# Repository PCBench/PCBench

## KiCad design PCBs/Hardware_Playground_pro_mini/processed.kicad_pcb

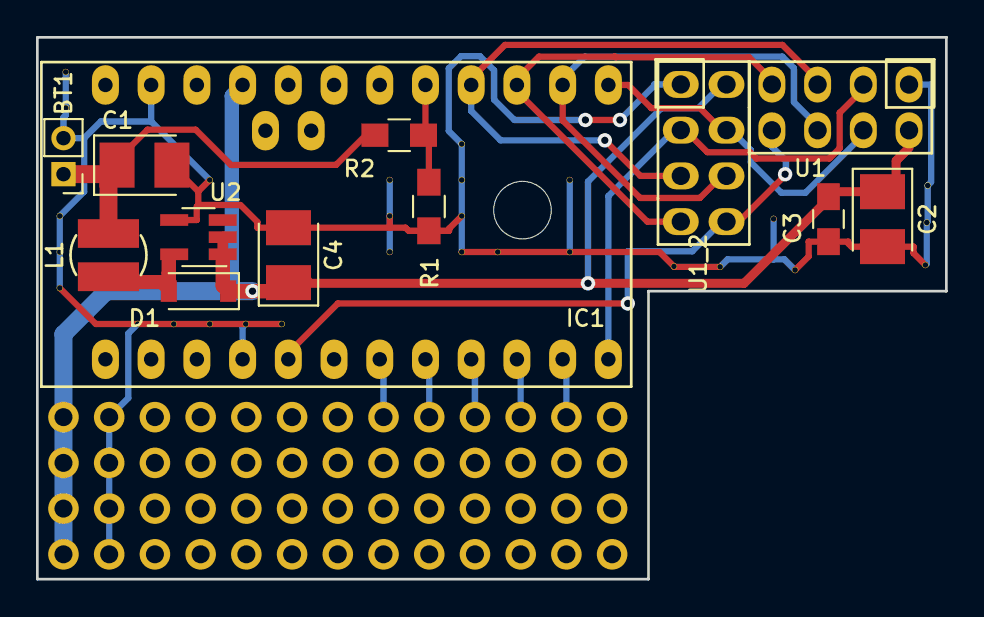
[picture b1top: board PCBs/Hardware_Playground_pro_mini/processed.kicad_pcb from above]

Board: 2 copper layers, 50.5 x 30.1 mm, 41 parts (0 on the bottom side), 11 nets.

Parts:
BT1: 3V; Pin_Header_Straight_1x02_Pitch2.00mm
C1: 10u; CP_Tantalum_Case-B_EIA-3528-21_Reflow
C2: 22u; CP_Tantalum_Case-B_EIA-3528-21_Reflow
C3: 100n; C_0805_HandSoldering
C4: 68u; CP_Tantalum_Case-B_EIA-3528-21_Reflow
D1: 1N5819; D_SOD-123
IC1: ArduinoProMini; pro_mini
L1: 47u; SDR0302
R1: 10K; R_0805_HandSoldering
R2: 22K; R_0805_HandSoldering
U1, U1_2: NRF24L01
U2: NCP1402; SOT-23-5_HandSoldering
V7_1, V7_2, V7_5, V7_6, V7_7, V9_8, V10_8, V11_4, V11_8, V12_8, V13_8, V16_4, V16_5, V16_6, V18_3, V18_4, V18_5, V18_6, V18_6_2, V18_6_3, V18_6_4, V18_6_5, V18_6_6, V18_6_7, V18_6_8, V19_6, V21_4, V21_6: AUTO_VIA; VIA_MATRIX

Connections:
+3.3V: C2.1, C3.1, C4.1, D1.1, IC1.21, U1.2, U1_2.2, U2.1, U2.2
/RF_CE: IC1.12, U1.3, U1_2.3
/RF_CSN: IC1.13, U1.4, U1_2.4
/RF_IRQ: IC1.5, U1.8, U1_2.8
/RF_MISO: IC1.15, U1.7, U1_2.7
/RF_MOSI: IC1.14, U1.6, U1_2.6
/RF_SCK: IC1.16, U1.5, U1_2.5
/V_BATT: IC1.17, R1.2, R2.2
GND: BT1.2, C1.2, C2.2, C3.2, C4.2, IC1.4, IC1.23, R1.1, U1.1, U1_2.1, U2.4, V7_1.1, V7_2.1, V7_5.1, V7_6.1, V7_7.1, V9_8.1, V10_8.1, V11_4.1, V11_8.1, V12_8.1, V13_8.1, V16_4.1, V16_5.1, V16_6.1, V18_3.1, V18_4.1, V18_5.1, V18_6.1, V18_6_2.1, V18_6_3.1, V18_6_4.1, V18_6_5.1, V18_6_6.1, V18_6_7.1, V18_6_8.1, V19_6.1, V21_4.1, V21_6.1
unnamed: BT1.1, C1.1, L1.1, R2.1
unnamed: D1.2, L1.2, U2.5

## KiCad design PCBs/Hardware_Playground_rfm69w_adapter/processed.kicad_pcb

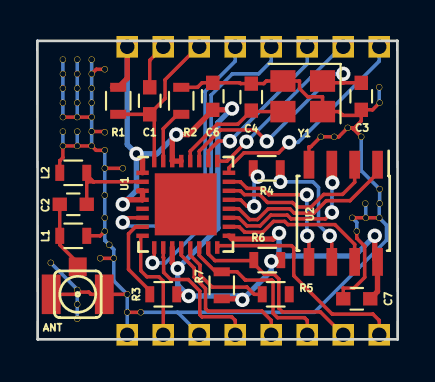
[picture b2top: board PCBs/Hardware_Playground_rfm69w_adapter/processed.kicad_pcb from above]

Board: 2 copper layers, 20.0 x 16.6 mm, 87 parts (0 on the bottom side), 29 nets.

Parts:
ANT: Antenna_Shield; coaxial_u.fl-r-smt-1
C1: 1u; C_0603
C2: 5p6; C_0603
C3, C4: 10p; C_0603
C6: 10u; C_0603
C7: 100n; C_0603
J1, J2, J3, J4, J5, J6, J7, J8, J9, J10, J11, J12, J13, J14, J15, J16: Conn_01x01; Pin_Header_Straight_1x01_Pitch2.00mm
L1, L2: DNP; L_0603
R1, R3, R5, R6, R7: 10K; R_0603
R2: 12K; R_0603
R4: 200; R_0603
U1: ESP8266EX; QFN-32-1EP_5x5mm_Pitch0.5mm
U2: AT25SF321-SSHDB; SOIC-8_3.9x4.9mm_Pitch1.27mm
V2_4, V2_5, V2_6, V2_7, V2_8, V2_9, V2_10, V3_4, V3_5, V3_6, V3_7, V3_8, V3_9, V3_10, V3_20, V3_21, V3_22, V4_4, V4_5, V4_5_2, V4_6, V4_7, V4_8, V4_9, V4_9_2, V4_10, V5_11, V5_11_2, V5_11_3, V7_21, V7_21_2, V7_21_3, V7_21_4, V7_21_5, V7_21_6, V7_21_7, V7_21_8, V7_21_9, V7_21_10, V22_9, V22_9_2, V22_9_3, V22_9_4, V22_9_5, V23_14, V23_14_2, V23_14_3, V23_14_4, V23_14_5, V24_7, V24_13, V24_14: AUTO_VIA; VIA_MATRIX
Y1: 26MHz; Crystal_SMD_3225-4pin_3.2x2.5mm

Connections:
+3V3: C6.2, C7.2, J9.1, R1.1, R3.1, R6.1, R7.1, U1.1, U1.3, U1.4, U1.11, U1.17, U1.29, U1.30, U2.8
/ADC: J15.1, U1.6
/DTR: C1.1, J13.1
/GPIO0: J8.1, R6.2, U1.15
/GPIO2: J1.1, R7.2, U1.14
/GPIO4: J2.1, U1.16
/GPIO5: J3.1, U1.24
/GPIO12: J4.1, U1.10
/GPIO13: J5.1, U1.12
/GPIO14: J6.1, U1.9
/GPIO16: J7.1, U1.8
/LNA: C2.2, L2.1, U1.2
/RESET: C1.2, J10.1, R1.2, U1.32
/SD_CLK: R4.1, U2.6
/SD_CS: U1.20, U2.1
/SD_HD: U1.18, U2.7
/SD_SI: U1.23, U2.5
/SD_SO: U1.22, U2.2
/SD_WP: U1.19, U2.3
/U0RX: J11.1, U1.26
/U0TX: J14.1, U1.25
GND: ANT.2, C3.2, C4.2, C6.1, C7.1, J12.1, J16.1, L1.2, L2.2, R2.1, U2.4, V2_4.1, V2_5.1, V2_6.1, V2_7.1, V2_8.1, V2_9.1, V2_10.1, V3_4.1, V3_5.1, V3_6.1, V3_7.1, V3_8.1, V3_9.1, V3_10.1, V3_20.1, V3_21.1, V3_22.1, V4_4.1, V4_5.1, V4_5_2.1, V4_6.1, V4_7.1, V4_8.1, V4_9.1, V4_9_2.1, V4_10.1, V5_11.1, V5_11_2.1, V5_11_3.1, V7_21.1, V7_21_2.1, V7_21_3.1, V7_21_4.1, V7_21_5.1, V7_21_6.1, V7_21_7.1, V7_21_8.1, V7_21_9.1, V7_21_10.1, V22_9.1, V22_9_2.1, V22_9_3.1, V22_9_4.1, V22_9_5.1, V23_14.1, V23_14_2.1, V23_14_3.1, V23_14_4.1, V23_14_5.1, V24_7.1, V24_13.1, V24_14.1, Y1.2, Y1.4
unnamed: ANT.1, C2.1, L1.1
unnamed: C3.1, U1.27, Y1.1
unnamed: C4.1, U1.28, Y1.3
unnamed: R2.2, U1.31
unnamed: R3.2, U1.7
unnamed: R4.2, U1.21
unnamed: R5.1, U1.13

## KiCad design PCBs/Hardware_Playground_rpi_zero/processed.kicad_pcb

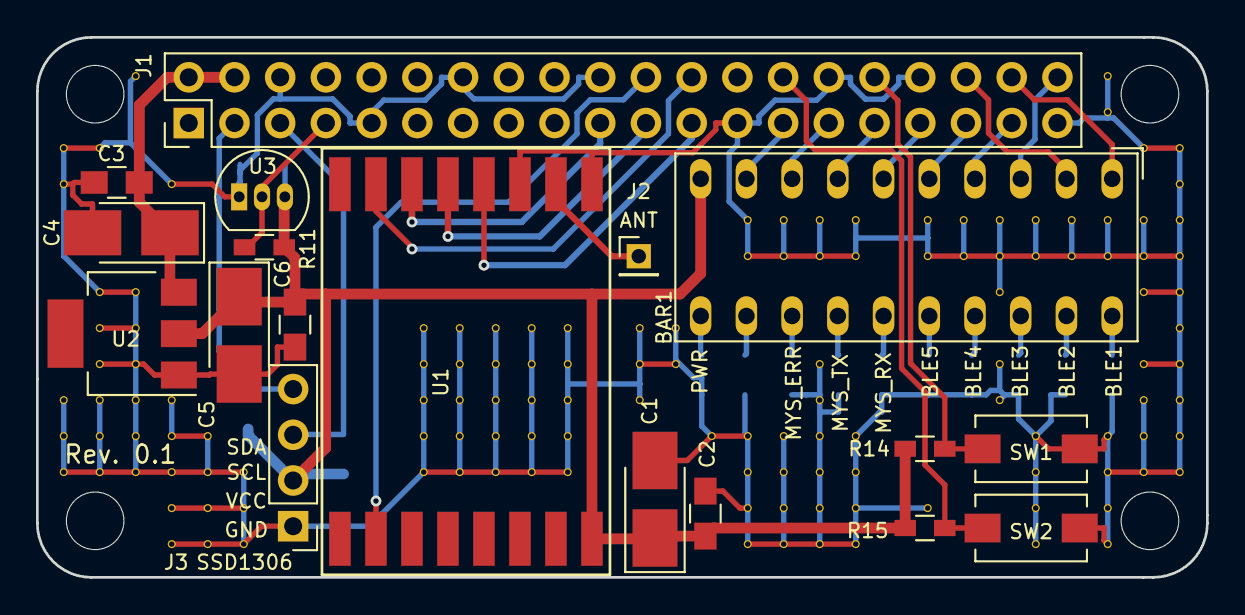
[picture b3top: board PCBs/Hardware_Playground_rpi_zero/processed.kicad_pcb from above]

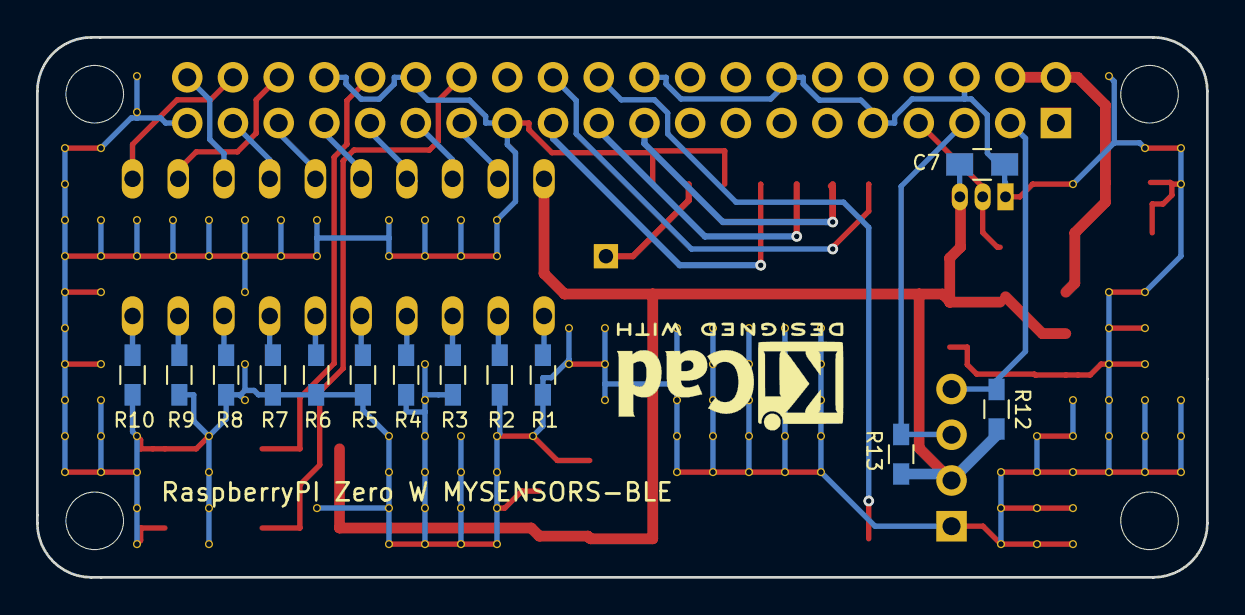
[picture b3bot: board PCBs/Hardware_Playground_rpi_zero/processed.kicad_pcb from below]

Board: 2 copper layers, 65.0 x 30.0 mm, 164 parts (13 on the bottom side), 33 nets.

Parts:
BAR1: HDSP-4850_2; HDSP-4850
C1, C4, C5: 22u; CP_Tantalum_Case-B_EIA-3528-21_Hand
C2, C3, C6, C7: 100n; C_0805_HandSoldering
J1: RPI_Zero_W; Pin_Header_Straight_2x20_Pitch2.54mm
J2: ANT; Pin_Header_Straight_1x01_Pitch2.00mm
J3: SSD1306; Pin_Header_Straight_1x04_Pitch2.54mm
R1, R2, R3, R4, R5, R6, R7, R8, R9, R10: 220; R_0603_HandSoldering
R11, R12, R13: 4K7; R_0603_HandSoldering
R14, R15: 10K; R_0603_HandSoldering
SW1, SW2: BLE; SW_SPST_EVQPE1
U1: RFM69HW; RFM69HW_SMD_Handsoldering
U2: AMS1117; SOT-223
U3: DS18B20; TO-92_Inline_Narrow_Oval
V3_4, V3_5, V3_11, V3_12, V3_13, V4_4, V4_8, V4_9, V4_10, V4_11, V4_12, V4_13, V5_2, V5_8, V5_9, V5_10, V5_11, V5_12, V5_13, V6_5, V6_11, V6_12, V6_13, V6_14, V6_15, V7_12, V7_13, V7_14, V7_15, V8_13, V8_14, V8_15, V13_9, V13_10, V13_11, V13_12, V13_13, V14_9, V14_10, V14_11, V14_12, V14_13, V15_9, V15_10, V15_11, V15_12, V15_13, V16_9, V16_10, V16_11, V16_12, V16_13, V17_9, V17_10, V17_11, V17_12, V17_13, V19_9, V19_10, V19_11, V20_9, V20_10, V21_12, V22_6, V22_7, V22_12, V22_13, V22_14, V22_15, V23_6, V23_7, V23_12, V23_13, V23_14, V23_15, V24_6, V24_7, V24_10, V24_11, V24_12, V24_13, V24_14, V24_15, V25_6, V25_7, V25_12, V25_13, V25_14, V25_15, V27_6, V27_7, V27_14, V28_6, V28_7, V29_6, V29_7, V29_8, V29_10, V29_11, V30_6, V30_7, V30_12, V30_13, V30_14, V30_15, V31_6, V31_7, V32_2, V32_3, V32_6, V32_7, V32_12, V32_13, V32_14, V32_15, V33_4, V33_6, V33_7, V33_8, V33_10, V33_11, V33_12, V33_13, V34_4, V34_5, V34_6, V34_7, V34_8, V34_9, V34_10, V34_11, V34_12, V34_13: AUTO_VIA; VIA_MATRIX

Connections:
+3V3: BAR1.10, C1.1, C2.2, C5.1, C6.2, C7.1, J3.2, R11.1, R12.2, R13.2, R14.1, R15.1, U1.8, U2.2, U3.3
+5V: C3.2, C4.1, J1.2, J1.4, U2.3
/RFM69_CE: J1.22, U1.2
/RFM69_CS: J1.24, U1.15
/RFM69_MISO: J1.21, U1.13
/RFM69_MOSI: J1.19, U1.14
/RFM69_SCK: J1.23, U1.12
/SSD_SCL: J1.5, J3.3, R13.1
/SSD_SDA: J1.3, J3.4, R12.1
/SW1: J1.32, R14.2, SW1.1
/SW2: J1.28, R15.2, SW2.1
GND: C1.2, C2.1, C3.1, C4.2, C5.2, C6.1, C7.2, J1.6, J1.9, J1.14, J1.20, J1.25, J1.30, J1.34, J1.39, J3.1, R1.2, R2.2, R3.2, R4.2, R5.2, R6.2, R7.2, R8.2, R9.2, R10.2, SW1.2, SW2.2, U1.9, U1.11, U2.1, U3.1, V3_4.1, V3_5.1, V3_11.1, V3_12.1, V3_13.1, V4_4.1, V4_8.1, V4_9.1, V4_10.1, V4_11.1, V4_12.1, V4_13.1, V5_2.1, V5_8.1, V5_9.1, V5_10.1, V5_11.1, V5_12.1, V5_13.1, V6_5.1, V6_11.1, V6_12.1, V6_13.1, V6_14.1, V6_15.1, V7_12.1, V7_13.1, V7_14.1, V7_15.1, V8_13.1, V8_14.1, V8_15.1, V13_9.1, V13_10.1, V13_11.1, V13_12.1, V13_13.1, V14_9.1, V14_10.1, V14_11.1, V14_12.1, V14_13.1, V15_9.1, V15_10.1, V15_11.1, V15_12.1, V15_13.1, V16_9.1, V16_10.1, V16_11.1, V16_12.1, V16_13.1, V17_9.1, V17_10.1, V17_11.1, V17_12.1, V17_13.1, V19_9.1, V19_10.1, V19_11.1, V20_9.1, V20_10.1, V21_12.1, V22_6.1, V22_7.1, V22_12.1, V22_13.1, V22_14.1, V22_15.1, V23_6.1, V23_7.1, V23_12.1, V23_13.1, V23_14.1, V23_15.1, V24_6.1, V24_7.1, V24_10.1, V24_11.1, V24_12.1, V24_13.1, V24_14.1, V24_15.1, V25_6.1, V25_7.1, V25_12.1, V25_13.1, V25_14.1, V25_15.1, V27_6.1, V27_7.1, V27_14.1, V28_6.1, V28_7.1, V29_6.1, V29_7.1, V29_8.1, V29_10.1, V29_11.1, V30_6.1, V30_7.1, V30_12.1, V30_13.1, V30_14.1, V30_15.1, V31_6.1, V31_7.1, V32_2.1, V32_3.1, V32_6.1, V32_7.1, V32_12.1, V32_13.1, V32_14.1, V32_15.1, V33_4.1, V33_6.1, V33_7.1, V33_8.1, V33_10.1, V33_11.1, V33_12.1, V33_13.1, V34_4.1, V34_5.1, V34_6.1, V34_7.1, V34_8.1, V34_9.1, V34_10.1, V34_11.1, V34_12.1, V34_13.1
unnamed: BAR1.1, J1.38
unnamed: BAR1.2, J1.36
unnamed: BAR1.3, J1.40
unnamed: BAR1.4, J1.37
unnamed: BAR1.5, J1.35
unnamed: BAR1.6, J1.33
unnamed: BAR1.7, J1.31
unnamed: BAR1.8, J1.29
unnamed: BAR1.9, J1.27
unnamed: BAR1.11, R1.1
unnamed: BAR1.12, R2.1
unnamed: BAR1.13, R3.1
unnamed: BAR1.14, R4.1
unnamed: BAR1.15, R5.1
unnamed: BAR1.16, R6.1
unnamed: BAR1.17, R7.1
unnamed: BAR1.18, R8.1
unnamed: BAR1.19, R9.1
unnamed: BAR1.20, R10.1
unnamed: J1.7, R11.2, U3.2
unnamed: J2.1, U1.10

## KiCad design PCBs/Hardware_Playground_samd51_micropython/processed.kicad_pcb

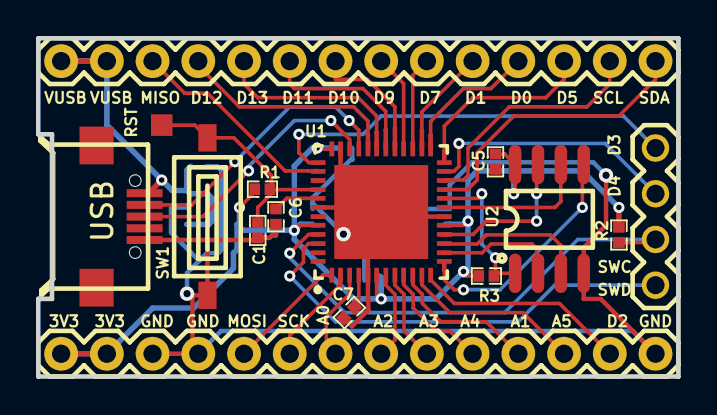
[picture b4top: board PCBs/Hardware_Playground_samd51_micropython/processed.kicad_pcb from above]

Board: 2 copper layers, 35.6 x 18.8 mm, 21 parts (0 on the bottom side), 39 nets.

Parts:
C1, C2, C3, C4, C7, C8, C9, C10: 1uF; 0402
C5: 100nF; 0402
C6: 10uF; 0402
H2: Header-Male-2.54_1x4; 210S-1X4P
JP1, JP2: M14; 1X14
R1: 10K; 0402
R2: 2K2; 0402
R3: 100K; 0402
SW1: RESET; SWITCH-3X6X2.5_SMD
U1: ATSAMD51G19A-MU; 48QFN7X7
U2: IS25LP016D-JBLE; SOIC-8
U3: AP2112K-3.3TRG1; SOT-25
USB: Micro USB-B 5P_C40942; MICRO-USB-12

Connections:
+3V3: C3.2, C4.1, C5.2, C8.1, C9.1, C10.2, JP2.13, JP2.14, R1.2, R2.2, R3.2, U1.6, U1.17, U1.36, U1.44, U2.8, U3.5
A0: JP2.8, U1.3
A1: JP2.4, U1.10
A2: JP2.7, U1.7
A3: JP2.6, U1.8
A4: JP2.5, U1.9
A5: JP2.3, U1.11
AREF: C7.1, U1.4
D2: JP2.2, U1.12
D3: H2.4, U1.37
D4: H2.3, U1.23
D5: JP1.12, U1.24
D7: JP1.9, U1.27
D9: JP1.8, U1.28
D10: JP1.7, U1.29
D11: JP1.6, U1.30
D12: JP1.4, U1.32
D13: JP1.5, U1.31
D+: U1.34, USB.3
D-: U1.33, USB.2
GND: C1.1, C2.2, C3.1, C4.2, C6.1, C7.2, C8.2, C9.2, C10.1, JP2.1, JP2.11, JP2.12, SW1.1, U1.5, U1.18, U1.35, U1.42, U1.49, U2.4, U3.2, USB.5
MISO: JP1.3, U1.38
MOSI: JP2.10, U1.1
QSPI_CS: R3.1, U1.20, U2.1
QSPI_DAT0: U1.13, U2.5
QSPI_DAT1: U1.14, U2.2
QSPI_DAT2: U1.15, U2.3
QSPI_DAT3: U1.16, U2.7
QSPI_SCK: U1.19, U2.6
RST: C1.2, R1.1, SW1.2, U1.40
RX_D0: JP1.11, U1.25
SCK: JP2.9, U1.2
SCL: JP1.13, U1.22
SDA: JP1.14, U1.21
SWCLK: H2.2, R2.1, U1.45
SWDIO: H2.1, U1.46
TX_D1: JP1.10, U1.26
U1_41: C6.2, U1.41
VUSB: C2.1, JP1.1, JP1.2, U3.1, U3.3, USB.1

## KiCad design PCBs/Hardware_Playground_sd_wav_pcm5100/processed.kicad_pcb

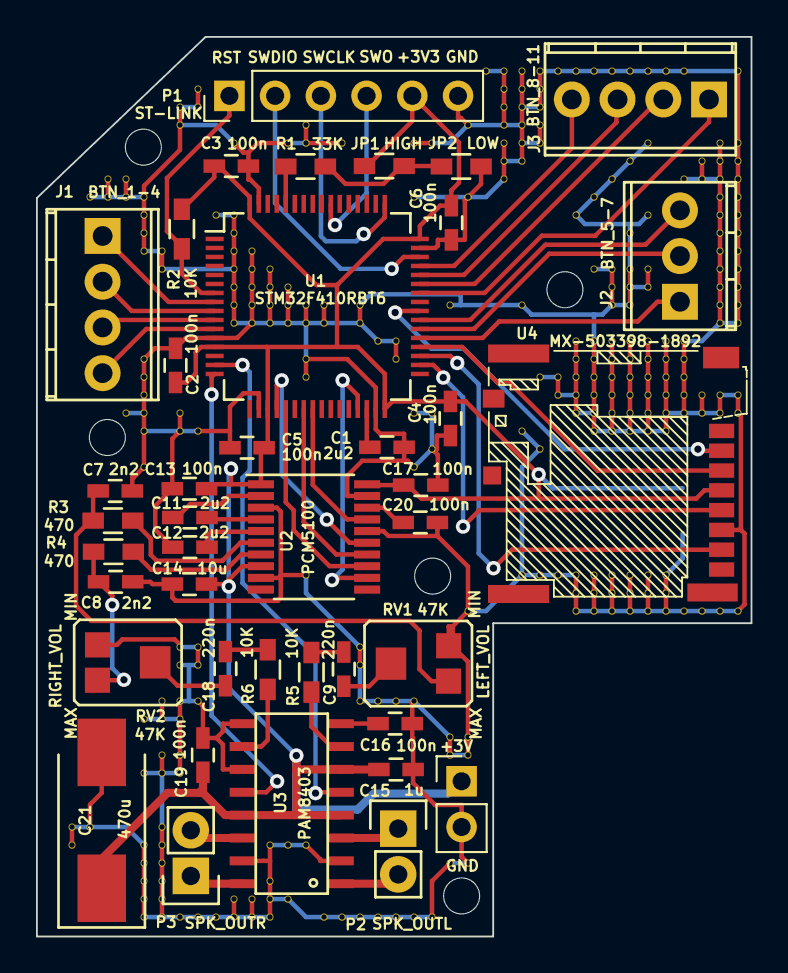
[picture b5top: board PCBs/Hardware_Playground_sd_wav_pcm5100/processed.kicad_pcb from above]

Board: 2 copper layers, 39.7 x 50.0 mm, 323 parts (1 on the bottom side), 50 nets.

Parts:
C1, C11, C14: 2u2; C_0603_HandSoldering
C2, C3, C4, C5, C6, C13, C16, C17, C19, C20: 100n; C_0603_HandSoldering
C7, C8: 2n2; C_0603_HandSoldering
C9, C18: 220n; C_0603_HandSoldering
C10: 47u; C_0805_HandSoldering
C12: 10u; C_0603_HandSoldering
C15: 1u; C_0603_HandSoldering
C21: 470u; Tantalum_Case-D_EIA-7343-31_Hand
J1: BTN_1-4; TerminalBlock_Pheonix_MPT-2.54mm_4pol
J2: BTN_5-7; TerminalBlock_Pheonix_MPT-2.54mm_3pol
J3: BTN_8-11; TerminalBlock_Pheonix_MPT-2.54mm_4pol
JP1: HIGH; R_0603_HandSoldering
JP2: LOW; R_0603_HandSoldering
P1: ST-LINK; Pin_Header_Straight_1x06_Pitch2.54mm
P2: SPK_OUTL; Pin_Header_Straight_1x02
P3: SPK_OUTR; Pin_Header_Straight_1x02
P4: Supply; Pin_Header_Straight_1x02_Pitch2.54mm
R1: 33K; R_0603_HandSoldering
R2, R5, R6: 10K; R_0603_HandSoldering
R3, R4: 470; R_0603_HandSoldering
RV1, RV2: 47K; TC-33X-2
U1: STM32F410RBT6; LQFP-64_10x10mm_Pitch0.5mm
U2: PCM5100; TSSOP-20_4.4x6.5mm_Pitch0.65mm
U3: PAM8403; SOP16L
U4: MX-503398-1892
V2_44, V2_45, V3_9, V3_44, V4_8, V4_9, V5_8, V5_9, V5_21, V6_9, V6_10, V6_11, V6_12, V6_18, V6_19, V6_20, V6_21, V6_22, V6_24, V6_38, V6_41, V6_45, V6_46, V6_47, V6_48, V6_49, V7_12, V7_13, V7_37, V7_38, V7_40, V7_41, V7_44, V7_45, V7_46, V7_47, V7_48, V7_49, V8_4, V8_5, V8_21, V8_22, V8_34, V8_35, V8_37, V8_38, V8_40, V8_41, V8_49, V9_3, V9_4, V9_22, V9_34, V9_35, V9_37, V9_49, V10_10, V10_49, V11_6, V11_10, V11_11, V11_12, V11_13, V11_14, V11_15, V11_16, V11_48, V11_49, V12_12, V12_13, V12_14, V12_15, V12_16, V12_48, V12_49, V13_13, V13_14, V13_15, V13_16, V13_45, V13_47, V13_48, V13_49, V14_6, V14_14, V14_15, V14_16, V14_45, V14_48, V15_5, V15_6, V15_15, V15_16, V15_18, V15_19, V15_30, V15_45, V16_15, V16_16, V16_49, V17_6, V17_49, V18_15, V18_16, V18_34, V18_35, V18_37, V18_49, V19_17, V19_37, V19_49, V20_17, V20_18, V20_37, V20_49, V21_6, V21_9, V21_21, V21_24, V21_37, V21_49, V22_6, V22_21, V22_23, V22_49, V23_15, V23_39, V23_40, V23_46, V24_5, V24_9, V24_32, V24_39, V24_40, V24_46, V25_2, V26_2, V26_3, V26_4, V26_5, V26_6, V26_7, V26_8, V27_2, V27_3, V27_4, V27_5, V27_6, V27_7, V27_15, V27_22, V27_30, V28_2, V28_3, V28_4, V28_5, V28_6, V28_19, V28_23, V28_30, V29_2, V29_19, V29_20, V29_30, V30_2, V30_10, V30_17, V30_18, V30_19, V30_20, V30_21, V30_30, V30_31, V30_32, V31_2, V31_9, V31_13, V31_17, V31_18, V31_19, V31_20, V31_21, V31_22, V31_30, V31_31, V31_32, V32_2, V32_8, V32_13, V32_14, V32_15, V32_17, V32_18, V32_19, V32_20, V32_21, V32_22, V32_30, V32_31, V32_32, V33_2, V33_7, V33_11, V33_13, V33_14, V33_15, V33_17, V33_18, V33_19, V33_20, V33_21, V33_22, V33_30, V33_31, V33_32, V34_2, V34_6, V34_10, V34_13, V34_14, V34_17, V34_18, V34_19, V34_20, V34_21, V34_22, V34_30, V34_31, V34_32, V35_2, V35_17, V35_18, V35_19, V35_20, V35_21, V35_22, V35_30, V35_31, V35_32, V36_2, V36_8, V36_17, V36_18, V36_19, V36_20, V36_21, V36_32, V37_7, V37_8, V37_20, V37_21, V37_32, V38_6, V38_7, V38_8, V38_9, V38_10, V38_11, V38_12, V38_13, V38_14, V38_15, V38_16, V38_20, V38_21, V38_32, V39_2, V39_6, V39_7, V39_8, V39_9, V39_10, V39_11, V39_12, V39_13, V39_14, V39_15, V39_16, V39_20, V39_21, V39_32: AUTO_VIA; VIA_MATRIX

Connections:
+3V3: C2.1, C3.1, C4.1, C5.1, C6.1, C10.1, C12.2, C13.1, C15.2, C17.1, C19.1, C21.1, JP1.2, P1.5, P4.1, R2.2, U1.13, U1.19, U1.32, U1.48, U1.64, U2.1, U2.8, U2.20, U3.4, U3.6, U3.13, U4.4
/BTN1: J1.1, U1.8
/BTN2: J1.2, U1.9
/BTN3: J1.3, U1.10
/BTN4: J1.4, U1.11
/BTN5: J2.1, U1.37
/BTN6: J2.2, U1.38
/BTN7: J2.3, U1.39
/BTN8: J3.1, U1.42
/BTN9: J3.2, U1.43
/BTN10: J3.3, U1.44
/BTN11: J3.4, U1.45
/I2S_BCLK: U1.21, U2.13
/I2S_DATA: U1.23, U2.14
/I2S_LRCLK: U1.20, U2.15
/I2S_MCLK: U1.29, U2.12
/PAM8403_MUTE: U1.15, U3.5
/PAM8403_STANDBY: U1.16, U3.12
/PCM5100_MUTE: U1.24, U2.17
/PCM5100_OUTL: C7.2, R3.2, RV1.1
/PCM5100_OUTR: C8.2, R4.2, RV2.3
/SD_CS: U1.40, U4.2
/SD_DI: U1.36, U4.3
/SD_DO: U1.35, U4.7
/SD_SCLK: U1.34, U4.5
/SWCLK: P1.3, U1.49
/SWDIO: P1.2, U1.46
/SWO: P1.4, U1.55
/nRST: P1.1, R2.1, U1.7
GND: C1.2, C2.2, C3.2, C4.2, C5.2, C6.2, C7.1, C8.1, C10.2, C12.1, C13.2, C14.2, C15.1, C16.1, C17.2, C19.2, C20.2, C21.2, JP2.1, P1.6, P4.2, RV1.3, RV2.1, U1.12, U1.18, U1.31, U1.47, U1.63, U2.3, U2.9, U2.16, U2.19, U3.2, U3.9, U3.11, U3.15, U4.6, V2_44.1, V2_45.1, V3_9.1, V3_44.1, V4_8.1, V4_9.1, V5_8.1, V5_9.1, V5_21.1, V6_9.1, V6_10.1, V6_11.1, V6_12.1, V6_18.1, V6_19.1, V6_20.1, V6_21.1, V6_22.1, V6_24.1, V6_38.1, V6_41.1, V6_45.1, V6_46.1, V6_47.1, V6_48.1, V6_49.1, V7_12.1, V7_13.1, V7_37.1, V7_38.1, V7_40.1, V7_41.1, V7_44.1, V7_45.1, V7_46.1, V7_47.1, V7_48.1, V7_49.1, V8_4.1, V8_5.1, V8_21.1, V8_22.1, V8_34.1, V8_35.1, V8_37.1, V8_38.1, V8_40.1, V8_41.1, V8_49.1, V9_3.1, V9_4.1, V9_22.1, V9_34.1, V9_35.1, V9_37.1, V9_49.1, V10_10.1, V10_49.1, V11_6.1, V11_10.1, V11_11.1, V11_12.1, V11_13.1, V11_14.1, V11_15.1, V11_16.1, V11_48.1, V11_49.1, V12_12.1, V12_13.1, V12_14.1, V12_15.1, V12_16.1, V12_48.1, V12_49.1, V13_13.1, V13_14.1, V13_15.1, V13_16.1, V13_45.1, V13_47.1, V13_48.1, V13_49.1, V14_6.1, V14_14.1, V14_15.1, V14_16.1, V14_45.1, V14_48.1, V15_5.1, V15_6.1, V15_15.1, V15_16.1, V15_18.1, V15_19.1, V15_30.1, V15_45.1, V16_15.1, V16_16.1, V16_49.1, V17_6.1, V17_49.1, V18_15.1, V18_16.1, V18_34.1, V18_35.1, V18_37.1, V18_49.1, V19_17.1, V19_37.1, V19_49.1, V20_17.1, V20_18.1, V20_37.1, V20_49.1, V21_6.1, V21_9.1, V21_21.1, V21_24.1, V21_37.1, V21_49.1, V22_6.1, V22_21.1, V22_23.1, V22_49.1, V23_15.1, V23_39.1, V23_40.1, V23_46.1, V24_5.1, V24_9.1, V24_32.1, V24_39.1, V24_40.1, V24_46.1, V25_2.1, V26_2.1, V26_3.1, V26_4.1, V26_5.1, V26_6.1, V26_7.1, V26_8.1, V27_2.1, V27_3.1, V27_4.1, V27_5.1, V27_6.1, V27_7.1, V27_15.1, V27_22.1, V27_30.1, V28_2.1, V28_3.1, V28_4.1, V28_5.1, V28_6.1, V28_19.1, V28_23.1, V28_30.1, V29_2.1, V29_19.1, V29_20.1, V29_30.1, V30_2.1, V30_10.1, V30_17.1, V30_18.1, V30_19.1, V30_20.1, V30_21.1, V30_30.1, V30_31.1, V30_32.1, V31_2.1, V31_9.1, V31_13.1, V31_17.1, V31_18.1, V31_19.1, V31_20.1, V31_21.1, V31_22.1, V31_30.1, V31_31.1, V31_32.1, V32_2.1, V32_8.1, V32_13.1, V32_14.1, V32_15.1, V32_17.1, V32_18.1, V32_19.1, V32_20.1, V32_21.1, V32_22.1, V32_30.1, V32_31.1, V32_32.1, V33_2.1, V33_7.1, V33_11.1, V33_13.1, V33_14.1, V33_15.1, V33_17.1, V33_18.1, V33_19.1, V33_20.1, V33_21.1, V33_22.1, V33_30.1, V33_31.1, V33_32.1, V34_2.1, V34_6.1, V34_10.1, V34_13.1, V34_14.1, V34_17.1, V34_18.1, V34_19.1, V34_20.1, V34_21.1, V34_22.1, V34_30.1, V34_31.1, V34_32.1, V35_2.1, V35_17.1, V35_18.1, V35_19.1, V35_20.1, V35_21.1, V35_22.1, V35_30.1, V35_31.1, V35_32.1, V36_2.1, V36_8.1, V36_17.1, V36_18.1, V36_19.1, V36_20.1, V36_21.1, V36_32.1, V37_7.1, V37_8.1, V37_20.1, V37_21.1, V37_32.1, V38_6.1, V38_7.1, V38_8.1, V38_9.1, V38_10.1, V38_11.1, V38_12.1, V38_13.1, V38_14.1, V38_15.1, V38_16.1, V38_20.1, V38_21.1, V38_32.1, V39_2.1, V39_6.1, V39_7.1, V39_8.1, V39_9.1, V39_10.1, V39_11.1, V39_12.1, V39_13.1, V39_14.1, V39_15.1, V39_16.1, V39_20.1, V39_21.1, V39_32.1
unnamed: C1.1, U1.30
unnamed: C9.1, R5.2
unnamed: C9.2, RV1.2
unnamed: C11.1, U2.4
unnamed: C11.2, U2.2
unnamed: C14.1, U2.5
unnamed: C16.2, U3.8
unnamed: C18.1, RV2.2
unnamed: C18.2, R6.1
unnamed: C20.1, U2.18
unnamed: JP1.1, JP2.2, R1.2
unnamed: P2.1, U3.3
unnamed: P2.2, U3.1
unnamed: P3.1, U3.16
unnamed: P3.2, U3.14
unnamed: R1.1, U1.60
unnamed: R3.1, U2.6
unnamed: R4.1, U2.7
unnamed: R5.1, U3.7
unnamed: R6.2, U3.10

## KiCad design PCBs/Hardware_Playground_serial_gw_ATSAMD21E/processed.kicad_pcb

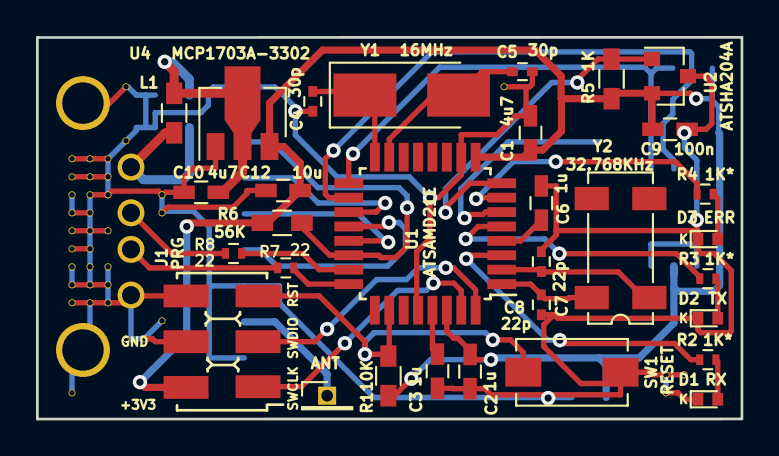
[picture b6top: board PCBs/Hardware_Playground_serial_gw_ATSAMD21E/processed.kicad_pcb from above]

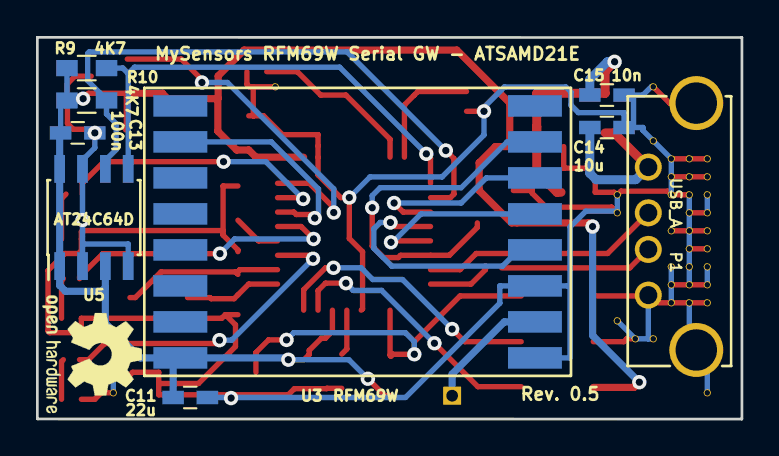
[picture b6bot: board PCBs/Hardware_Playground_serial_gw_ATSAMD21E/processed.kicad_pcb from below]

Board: 2 copper layers, 39.1 x 21.2 mm, 77 parts (8 on the bottom side), 32 nets.

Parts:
C1, C10: 4u7; C_0603_HandSoldering
C2, C3, C6: 1u; C_0603_HandSoldering
C4, C5: 30p; C_0402
C7, C8: 22p; C_0402
C9, C13: 100n; C_0603_HandSoldering
C11: 22u; C_0603_HandSoldering
C12, C14: 10u; C_0603_HandSoldering
C15: 10n; C_0603_HandSoldering
D1: RX; LED_0402
D2: TX; LED_0402
D3: ERR; LED_0402
J1: PRG; AVR_ISP_SMT_Small_02x03
L1: BLM18HE152SN1D; R_0603_HandSoldering
P1: USB_A; USB_A_bottom
P2: ANT; Pin_Header_Straight_1x01_Pitch1.27mm
R1: 10K; R_0603_HandSoldering
R2, R3, R4: 1K*; R_0402
R5: 1K; R_0603_HandSoldering
R6: 56K; R_0603_HandSoldering
R7, R8: 22; R_0402
R9, R10: 4K7; R_0603_HandSoldering
SW1: RESET; SW_SPST_EVQPE1
U1: ATSAMD21E; TQFP-32_7x7mm_Pitch0.8mm
U2: ATSHA204A; SOT-23
U3: RFM69W; RFM69HW_SMD_Handsoldering
U4: MCP1703A-3302; SOT89-3_Housing
U5: AT24C64D; SOIC-8_3.9x4.9mm_Pitch1.27mm
V2_7, V2_8, V2_9, V2_10, V2_11, V2_12, V2_13, V2_14, V2_15, V2_20, V3_7, V3_8, V3_9, V3_10, V3_11, V3_12, V3_13, V3_14, V3_15, V4_7, V4_8, V4_9, V4_11, V4_13, V4_14, V4_15, V5_3, V5_6, V5_17, V6_17, V7_9, V7_10, V7_16, V26_3, V35_19, V35_20, V36_19: AUTO_VIA; VIA_MATRIX
Y1: 16MHz; Crystal_SMD_5032-2pin_5.0x3.2mm_HandSoldering
Y2: 32.768KHz; Crystal_SMD_SeikoEpson_MC306-4pin_8.0x3.2mm

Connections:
+3V3: C1.1, C2.2, C9.1, C11.1, C12.1, C13.1, J1.2, R1.2, R5.2, R6.2, R9.2, R10.2, U1.9, U1.30, U2.2, U3.8, U4.3, U5.1, U5.3, U5.8
/ATSHA204A: R5.1, U1.8, U2.1
/GW_ERR_LED: R4.2, U1.7
/GW_RX_LED: R2.2, U1.3
/GW_TX_LED: R3.2, U1.5
/MISO: U1.21, U3.13
/MOSI: U1.19, U3.14
/RFM69W_INT: U1.6, U3.2
/RFM69W_SS: R6.1, U1.22, U3.15
/RST: J1.5, R1.1, SW1.1, U1.26
/SCK: U1.20, U3.12
/SCL: R10.1, U1.18, U5.6
/SDA: R9.1, U1.17, U5.5
/SWCLK: J1.1, U1.31
/SWDIO: J1.3, U1.32
/USBDM: R8.1, U1.23
/USBDP: R7.1, U1.24
/VBUS: C10.1, C15.2, L1.2, U4.2
GND: C1.2, C2.1, C3.2, C4.2, C5.2, C6.2, C7.2, C8.2, C9.2, C10.2, C11.2, C12.2, C13.2, C14.1, C15.1, D1.1, D2.1, D3.1, J1.4, J1.6, P1.4, P1.5, SW1.2, U1.10, U1.28, U2.3, U3.9, U3.11, U4.1, U5.2, U5.4, U5.7, V2_7.1, V2_8.1, V2_9.1, V2_10.1, V2_11.1, V2_12.1, V2_13.1, V2_14.1, V2_15.1, V2_20.1, V3_7.1, V3_8.1, V3_9.1, V3_10.1, V3_11.1, V3_12.1, V3_13.1, V3_14.1, V3_15.1, V4_7.1, V4_8.1, V4_9.1, V4_11.1, V4_13.1, V4_14.1, V4_15.1, V5_3.1, V5_6.1, V5_17.1, V6_17.1, V7_9.1, V7_10.1, V7_16.1, V26_3.1, V35_19.1, V35_20.1, V36_19.1
unnamed: C3.1, U1.29
unnamed: C4.1, U1.16, Y1.1
unnamed: C5.1, U1.15, Y1.2
unnamed: C6.1, U1.4
unnamed: C7.1, U1.2, Y2.1
unnamed: C8.1, U1.1, Y2.4
unnamed: C14.2, L1.1, P1.1
unnamed: D1.2, R2.1
unnamed: D2.2, R3.1
unnamed: D3.2, R4.1
unnamed: P1.2, R8.2
unnamed: P1.3, R7.2
unnamed: P2.1, U3.10

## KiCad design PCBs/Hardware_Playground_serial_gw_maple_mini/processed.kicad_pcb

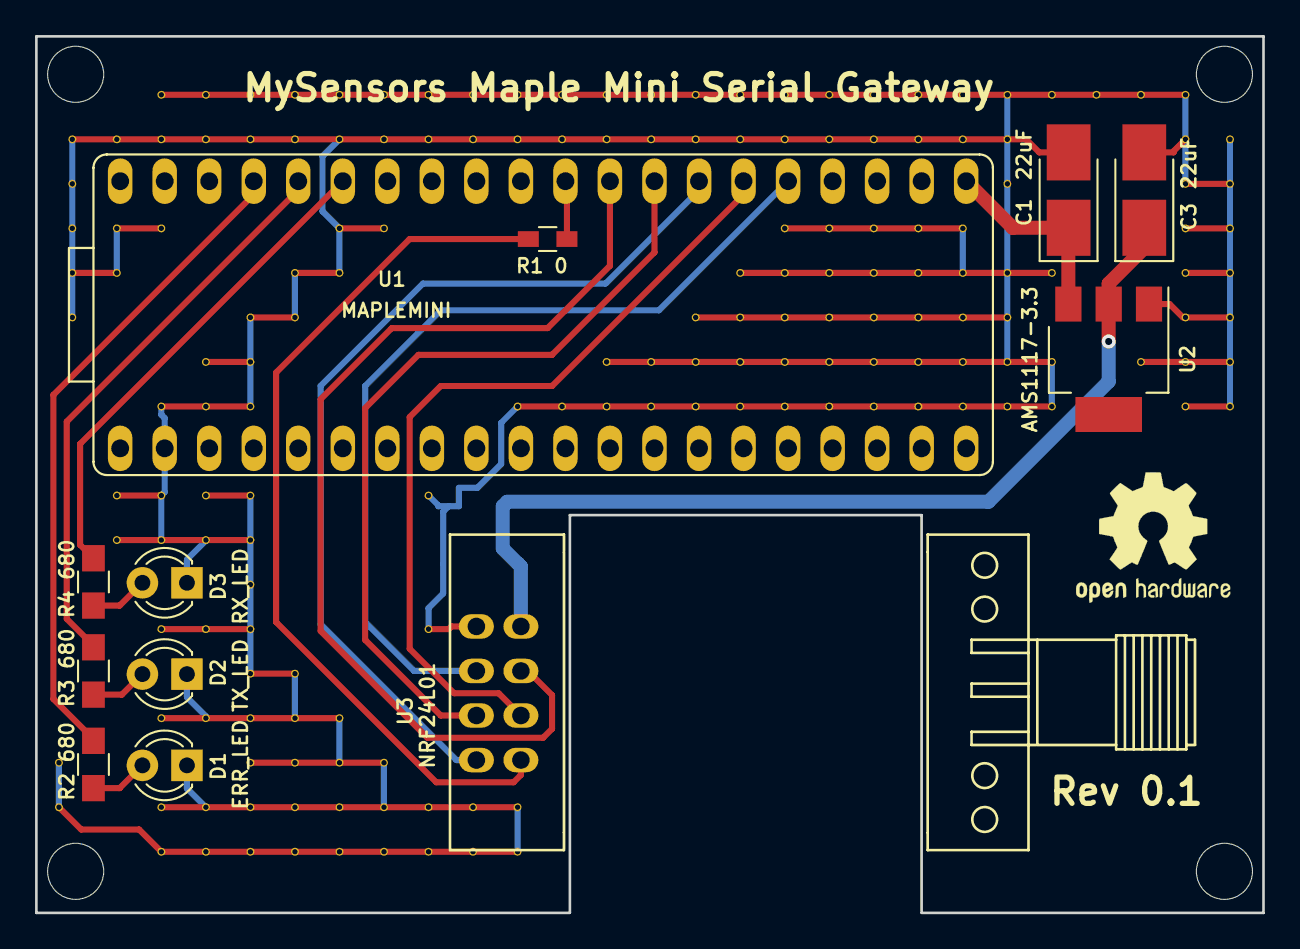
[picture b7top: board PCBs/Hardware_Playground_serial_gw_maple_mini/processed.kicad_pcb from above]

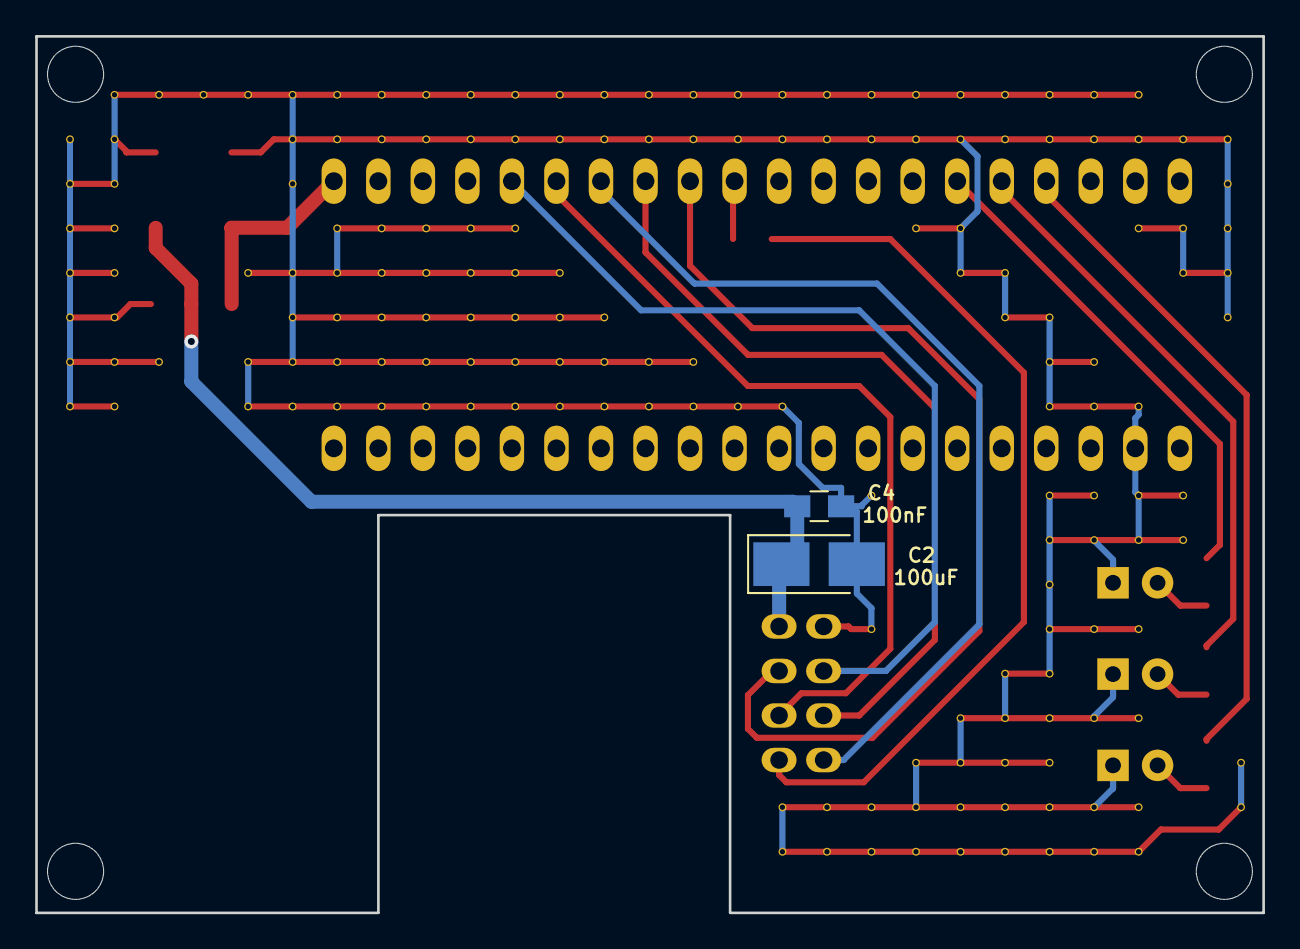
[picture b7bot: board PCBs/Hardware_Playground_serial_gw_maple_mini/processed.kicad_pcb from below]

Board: 2 copper layers, 70.0 x 50.0 mm, 184 parts (2 on the bottom side), 16 nets.

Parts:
C1, C3: 22uF; CP_Tantalum_Case-B_EIA-3528-21_Hand
C2: 100uF; CP_Tantalum_Case-B_EIA-3528-21_Hand
C4: 100nF; C_0805_HandSoldering
D1: ERR_LED; LED_D3.0mm
D2: TX_LED; LED_D3.0mm
D3: RX_LED; LED_D3.0mm
R1: 0; R_0603_HandSoldering
R2, R3, R4: 680; R_0805_HandSoldering
U1: MAPLEMINI; MAPLE_MINI
U2: AMS1117-3.3; SOT-223
U3: NRF24L01; E01-ML01DP5
V3_4, V3_5, V3_6, V3_7, V3_8, V3_18, V3_19, V4_4, V4_6, V4_7, V4_12, V4_13, V5_3, V5_4, V5_6, V5_10, V5_12, V5_13, V5_15, V5_17, V5_19, V5_20, V6_3, V6_4, V6_9, V6_10, V6_12, V6_13, V6_15, V6_17, V6_19, V6_20, V7_3, V7_4, V7_8, V7_9, V7_10, V7_12, V7_13, V7_14, V7_15, V7_16, V7_17, V7_18, V7_19, V7_20, V8_3, V8_4, V8_7, V8_8, V8_16, V8_17, V8_18, V8_19, V8_20, V9_3, V9_4, V9_6, V9_7, V9_17, V9_18, V9_19, V9_20, V10_3, V10_4, V10_6, V10_18, V10_19, V10_20, V11_3, V11_4, V11_12, V11_15, V11_19, V11_20, V12_3, V12_4, V12_19, V12_20, V13_3, V13_4, V13_10, V13_19, V13_20, V14_3, V14_4, V14_10, V15_3, V15_4, V15_9, V15_10, V16_3, V16_4, V16_9, V16_10, V17_3, V17_4, V17_8, V17_9, V17_10, V18_3, V18_4, V18_7, V18_8, V18_9, V18_10, V19_3, V19_4, V19_6, V19_7, V19_8, V19_9, V19_10, V20_3, V20_4, V20_6, V20_7, V20_8, V20_9, V20_10, V21_3, V21_4, V21_6, V21_7, V21_8, V21_9, V21_10, V22_3, V22_4, V22_6, V22_7, V22_8, V22_9, V22_10, V23_3, V23_4, V23_6, V23_7, V23_8, V23_9, V23_10, V24_3, V24_4, V24_5, V24_7, V24_8, V24_9, V24_10, V25_3, V25_7, V25_9, V25_10, V26_3, V27_3, V27_9, V28_3, V28_4, V28_5, V28_6, V28_7, V28_8, V28_9, V28_10, V29_4, V29_5, V29_6, V29_7, V29_8, V29_9, V29_10: AUTO_VIA; VIA_MATRIX

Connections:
+3V3: C2.1, C3.1, C4.1, U2.2, U3.2
/ERR_LED: R2.2, U1.37
/MAPLE_VIN: C1.1, U1.21, U2.3
/NRF24_IRQ: R1.1, U3.8
/RX_LED: R4.2, U1.35
/SPI_CE: U1.25, U3.3
/SPI_CSN: U1.29, U3.4
/SPI_MISO: U1.27, U3.7
/SPI_MOSI: U1.26, U3.6
/SPI_SCK: U1.28, U3.5
/TX_LED: R3.2, U1.36
GND: C1.2, C2.2, C3.2, C4.2, D1.1, D2.1, D3.1, U1.2, U2.1, U3.1, V3_4.1, V3_5.1, V3_6.1, V3_7.1, V3_8.1, V3_18.1, V3_19.1, V4_4.1, V4_6.1, V4_7.1, V4_12.1, V4_13.1, V5_3.1, V5_4.1, V5_6.1, V5_10.1, V5_12.1, V5_13.1, V5_15.1, V5_17.1, V5_19.1, V5_20.1, V6_3.1, V6_4.1, V6_9.1, V6_10.1, V6_12.1, V6_13.1, V6_15.1, V6_17.1, V6_19.1, V6_20.1, V7_3.1, V7_4.1, V7_8.1, V7_9.1, V7_10.1, V7_12.1, V7_13.1, V7_14.1, V7_15.1, V7_16.1, V7_17.1, V7_18.1, V7_19.1, V7_20.1, V8_3.1, V8_4.1, V8_7.1, V8_8.1, V8_16.1, V8_17.1, V8_18.1, V8_19.1, V8_20.1, V9_3.1, V9_4.1, V9_6.1, V9_7.1, V9_17.1, V9_18.1, V9_19.1, V9_20.1, V10_3.1, V10_4.1, V10_6.1, V10_18.1, V10_19.1, V10_20.1, V11_3.1, V11_4.1, V11_12.1, V11_15.1, V11_19.1, V11_20.1, V12_3.1, V12_4.1, V12_19.1, V12_20.1, V13_3.1, V13_4.1, V13_10.1, V13_19.1, V13_20.1, V14_3.1, V14_4.1, V14_10.1, V15_3.1, V15_4.1, V15_9.1, V15_10.1, V16_3.1, V16_4.1, V16_9.1, V16_10.1, V17_3.1, V17_4.1, V17_8.1, V17_9.1, V17_10.1, V18_3.1, V18_4.1, V18_7.1, V18_8.1, V18_9.1, V18_10.1, V19_3.1, V19_4.1, V19_6.1, V19_7.1, V19_8.1, V19_9.1, V19_10.1, V20_3.1, V20_4.1, V20_6.1, V20_7.1, V20_8.1, V20_9.1, V20_10.1, V21_3.1, V21_4.1, V21_6.1, V21_7.1, V21_8.1, V21_9.1, V21_10.1, V22_3.1, V22_4.1, V22_6.1, V22_7.1, V22_8.1, V22_9.1, V22_10.1, V23_3.1, V23_4.1, V23_6.1, V23_7.1, V23_8.1, V23_9.1, V23_10.1, V24_3.1, V24_4.1, V24_5.1, V24_7.1, V24_8.1, V24_9.1, V24_10.1, V25_3.1, V25_7.1, V25_9.1, V25_10.1, V26_3.1, V27_3.1, V27_9.1, V28_3.1, V28_4.1, V28_5.1, V28_6.1, V28_7.1, V28_8.1, V28_9.1, V28_10.1, V29_4.1, V29_5.1, V29_6.1, V29_7.1, V29_8.1, V29_9.1, V29_10.1
unnamed: D1.2, R2.1
unnamed: D2.2, R3.1
unnamed: D3.2, R4.1
unnamed: R1.2, U1.30
